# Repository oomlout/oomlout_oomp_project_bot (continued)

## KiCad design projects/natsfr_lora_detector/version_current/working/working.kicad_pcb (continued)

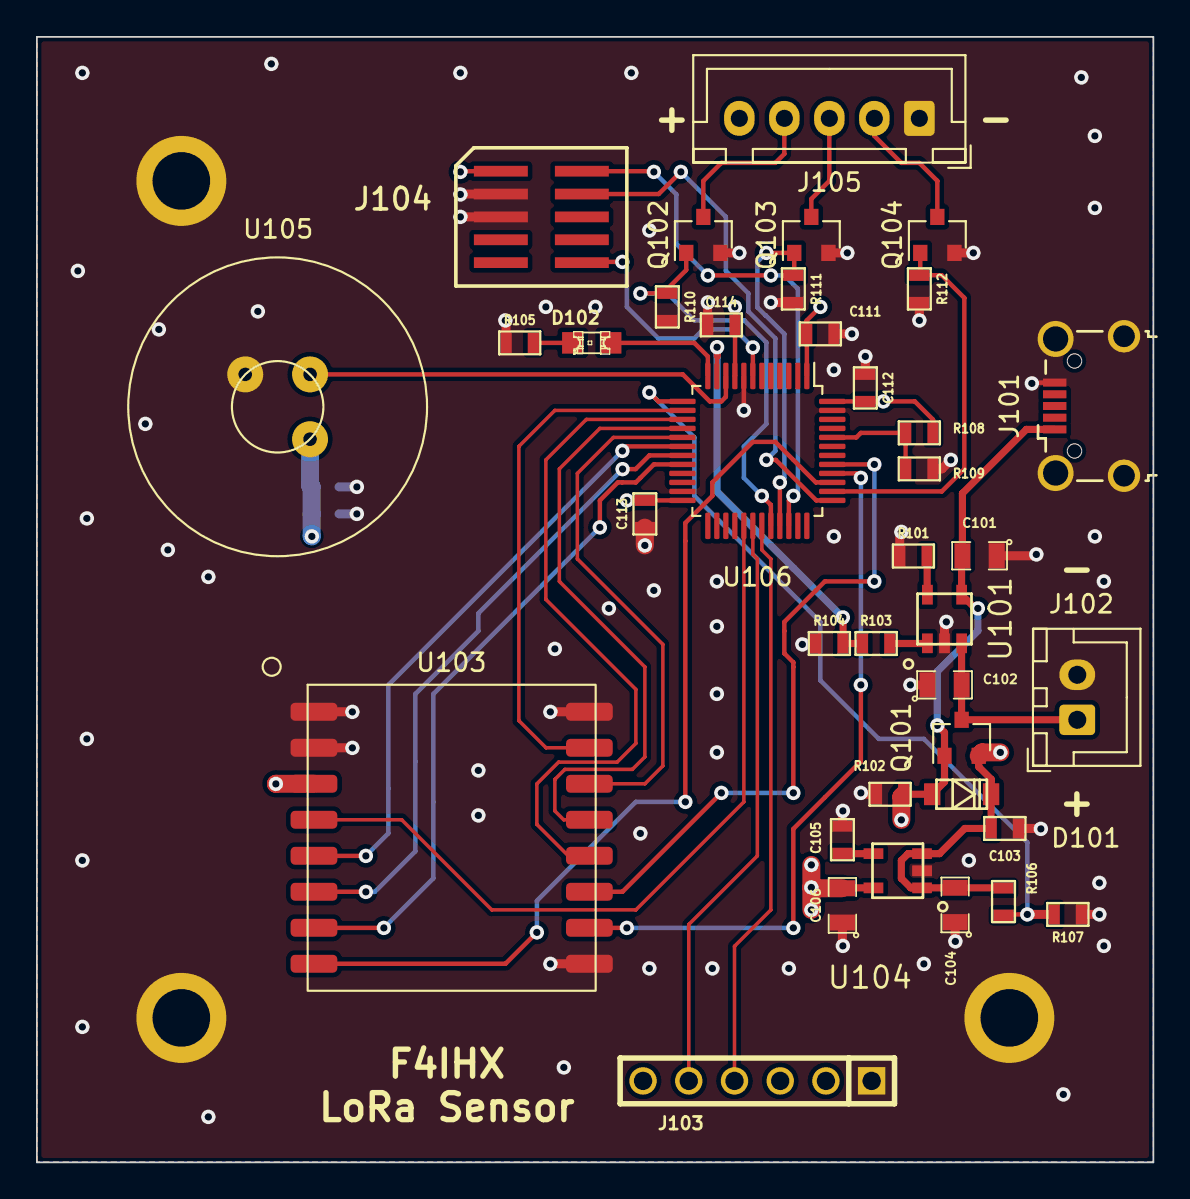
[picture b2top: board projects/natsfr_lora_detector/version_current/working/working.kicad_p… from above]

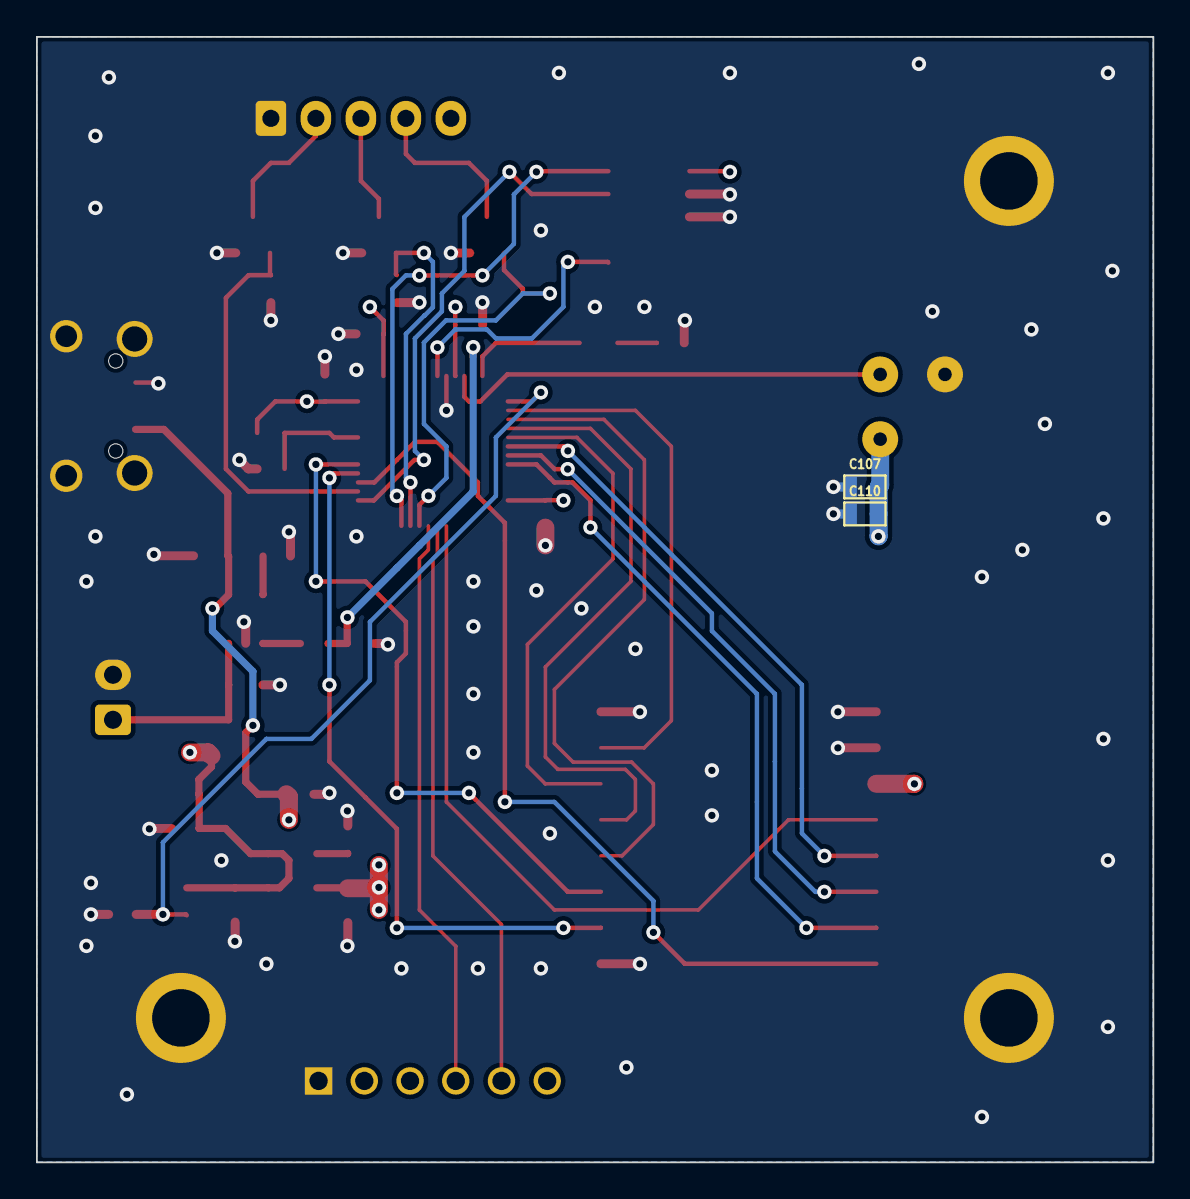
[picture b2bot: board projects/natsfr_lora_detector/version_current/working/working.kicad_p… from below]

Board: 4 copper layers, 62.0 x 62.5 mm, 40 parts (2 on the bottom side), 36 nets.

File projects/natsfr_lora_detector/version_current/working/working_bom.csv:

"Id";"Designator";"Footprint";"Quantity";"Designation";"Supplier and ref";
1;"C111,C113,C114,C112,C110,C107";"SM0603";6;"100nF";;;
2;"R110,R112,R111,R104";"SM0603";4;"10k";;;
3;"C103";"SM0603";1;"1uF";;;
4;"J102";"JST_XH_B2B-XH-A_1x02_P2.50mm_Vertical";1;"Battery";;;
5;"C101,C104,C106,C102";"SM0805";4;"4.7uF";;;
6;"D101";"SOD-123";1;"SCHOTTKY";;;
7;"J101";"USB_Micro-B_Wuerth_629105150521_CircularHoles";1;"USB_OTG";;;
8;"Q103,Q104,Q102";"SOT-23";3;"BSS138";;;
9;"REF**,REF**,REF**";"3.2mm_plated";3;"3.2mm_plated";;;
10;"R106,R101,R102,R109,R107";"SM0603";5;"12k";;;
11;"R108";"SM0603";1;"NC";;;
12;"C105";"SM0603";1;"10nF";;;
13;"U105";"EKMB439311xK";1;"EKMB439311xK";;;
14;"J105";"JST_XH_B5B-XH-A_1x05_P2.50mm_Vertical";1;"Conn_01x05";;;
15;"R105";"SM0603";1;"220";;;
16;"J103";"pin_array_6x1";1;"Conn_01x06_Male";;;
17;"J104";"JTAG_10ARM";1;"ARM_10x2mm";;;
18;"R103";"SM0603";1;"6.8k";;;
19;"D102";"LED-0805";1;"LED";;;
20;"U104";"SOT23-5";1;"REG113-XX-SOT23";;;
21;"U101";"SOT23-5";1;"MCP73821_2_SOT-23-5";;;
22;"U103";"RA-02_Lora";1;"RA-02_uFL";;;
23;"U106";"LQFP-48_7x7mm_P0.5mm";1;"STM32F051C8Tx";;;
24;"Q101";"SOT-23";1;"IRLML2244";;;

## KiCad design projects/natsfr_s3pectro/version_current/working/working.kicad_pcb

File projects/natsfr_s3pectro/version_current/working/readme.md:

# OOMP Project  
## s3pectro  by natsfr  
  
oomp key: oomp_projects_flat_natsfr_s3pectro  
(snippet of original readme)  
  
- s3pector  
Solid State Spectrometer front end  
  
  full source readme at [readme_src.md](readme_src.md)  
  
source repo at: [https://github.com/natsfr/s3pectro](https://github.com/natsfr/s3pectro)  
## Board  

## Schematic  

[schematic pdf](working_schematic.pdf)  
## Images

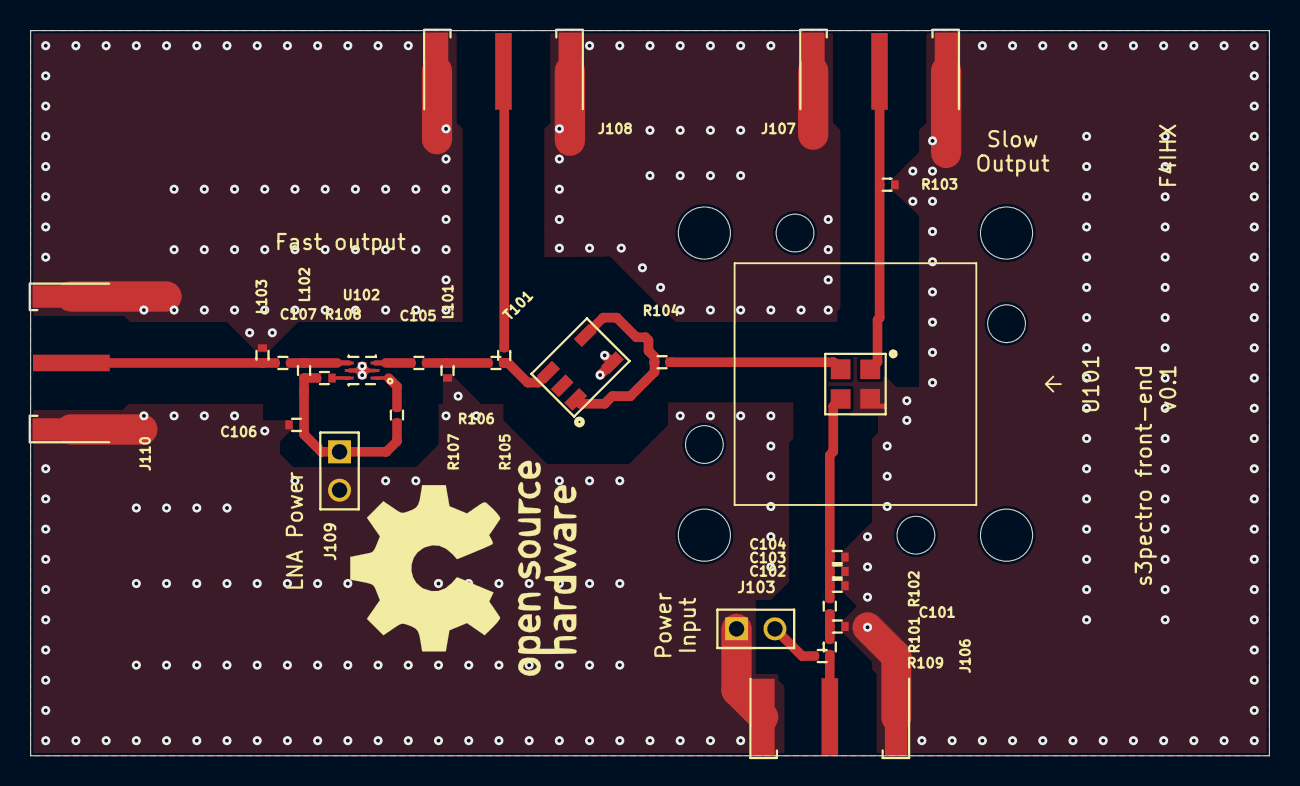
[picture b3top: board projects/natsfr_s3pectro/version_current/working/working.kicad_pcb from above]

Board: 4 copper layers, 82.0 x 48.0 mm, 32 parts (0 on the bottom side), 17 nets.

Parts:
C101, C102, C103, C104: 10n; SM0402
C105, C107: 33p; SM0402
C106: 100nF; SM0402
J101, J102, J104, J105: Conn_01x01; 3.45MM_NOTPLATED
J103, J109: Conn_01x02; pin_array_2x1
J106, J107, J108, J110: SMA_142-0701-801; CINCH_142-0701-801
L101: 18nH; SM0402
L102: 33nH; SM0402
L103: NC; SM0402
R101, R102, R103: 49.9R; SM0402
R104, R105, R106, R109: 0R; SM0402
R107, R108: 75R; SM0402
T101: MABACT0059
U101: MICROFB-30035; MicroFC-30035-SMT
U102: GRF2133; DFN-6_EP_1.5x1.5_Pitch0.5mm

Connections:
/LEN: R107.2, U102.1
/LNA_POW: C106.1, J109.1, L102.2, R107.1, R108.2
/LNA_Vdd: R108.1, U102.6
/RF_slow_out: J107.1, R103.1, U101.1
/RFo: R104.1, U101.2
/RFo_0: C107.2, J110.1, L103.2
/RFo_1: C107.1, L102.1, U102.4
/RFo_2: C105.2, U102.3
/RFo_3: C105.1, L101.2, R106.2
/RFo_4: R105.1, R106.1, T101.3
/RFo_n: J108.1, R105.2
/RFo_t: R104.2, T101.1, T101.4
/RFpi: C102.2, C103.2, C104.2, R102.2, U101.3
/RFpi_0: J106.1, R101.1, R109.2
/RFpi_1: C101.2, R101.2, R102.1
/RFpi_p: J103.2, R109.1
GND: C101.1, C102.1, C103.1, C104.1, C106.2, J103.1, J106.2, J107.2, J108.2, J109.2, J110.2, L101.1, L103.1, R103.2, T101.5, U101.4, U102.2, U102.5, U102.7

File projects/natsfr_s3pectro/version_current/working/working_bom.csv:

"Id";"Designator";"Footprint";"Quantity";"Designation";"Supplier and ref";
1;"J102,J105,J104,J101";"3.45MM_NOTPLATED";4;"Conn_01x01";;;
2;"R109,R106,R105,R104";"SM0402";4;"0R";;;
3;"R108,R107";"SM0402";2;"75R";;;
4;"R103,R102,R101";"SM0402";3;"49.9R";;;
5;"L103";"SM0402";1;"NC";;;
6;"L102";"SM0402";1;"33nH";;;
7;"L101";"SM0402";1;"18nH";;;
8;"C107,C105";"SM0402";2;"33p";;;
9;"C106";"SM0402";1;"100nF";;;
10;"C104,C103,C102,C101";"SM0402";4;"10n";;;
11;"G***";"OpenHardware";1;"LOGO";;;
12;"REF**,REF**,REF**,REF**";"2.5mm_non_plated";4;"2.5mm_non_plated";;;
13;"J109,J103";"pin_array_2x1";2;"Conn_01x02";;;
14;"U101";"MicroFC-30035-SMT";1;"MICROFB-30035";;;
15;"U102";"DFN-6_EP_1.5x1.5_Pitch0.5mm";1;"GRF2133";;;
16;"T101";"MABACT0059";1;"MABACT0059";;;
17;"J110,J108,J107,J106";"CINCH_142-0701-801";4;"SMA_142-0701-801";;;

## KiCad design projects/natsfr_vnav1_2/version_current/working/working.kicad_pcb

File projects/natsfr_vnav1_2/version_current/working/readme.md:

# VNAV1.2 by natsfr  
This is a harvested standardized copy of a project from github.  
The original project can be found at:  
https://github.com/natsfr/VNAV1.2  
Please consult that link for additional, details, files, and license information.  
Note: It was auto harvested and if the original repo had more than one board file or anything out of the ordinary the files here are likely not representative.

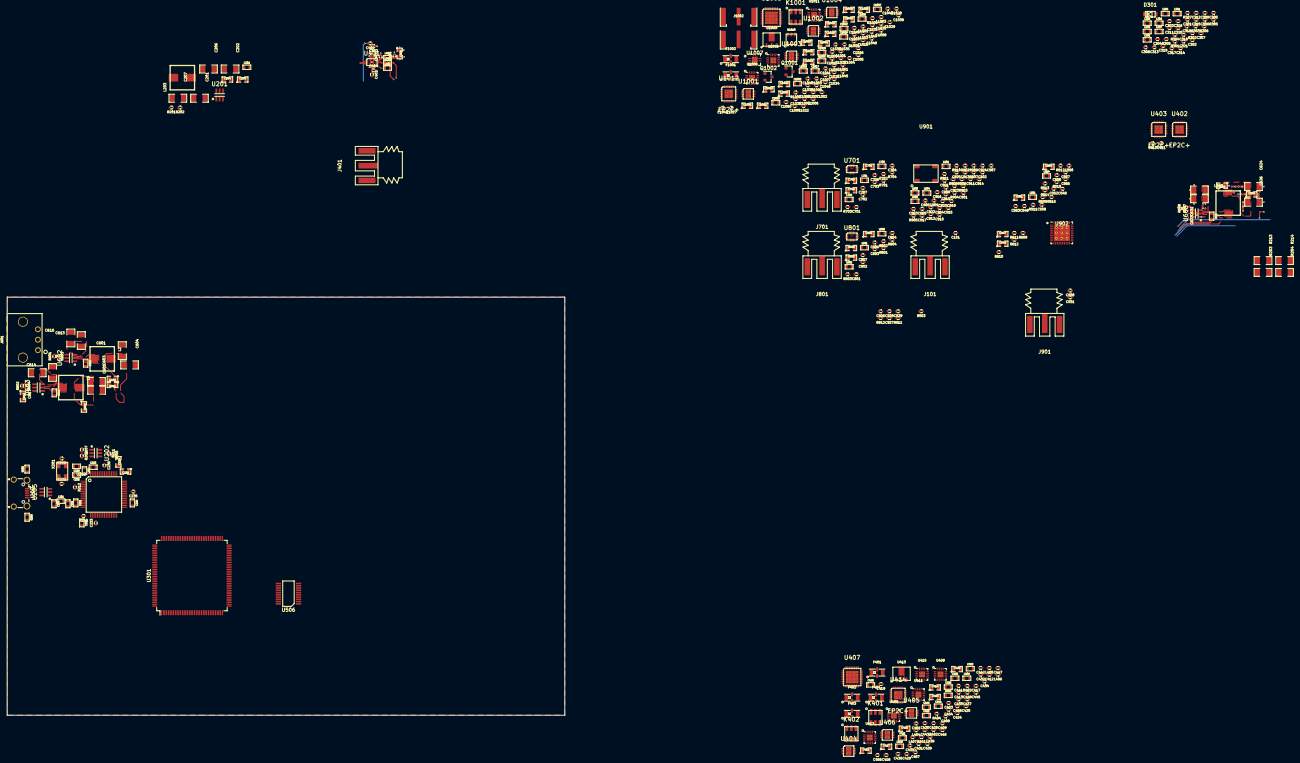
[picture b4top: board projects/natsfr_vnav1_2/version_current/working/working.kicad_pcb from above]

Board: 4 copper layers, 160.0 x 120.0 mm, 419 parts (1 on the bottom side), 264 nets.

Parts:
C101, C401, C402, C403, C404, C406, C407, C410, C411, C701, C702, C703, C704, C706, C707, C801, C802, C803, C804, C806, C807: CAP_0402; SM0402
C201, C202, C206, C207, C601, C603, C604, C605, C613, C614, C616, C617, C624, C626, C631, C633: 10uF; SM1206
C204, C608, C609, C628: 100nF; SM0805
C205, C611, C612, C630, C1050, C1051, C1053, C1056: 1uF; SM0805
C208, C618, C619, C637: 100nF; SM0603
C221, C223, C224: 100n; SM0603
C222, C226: 10p; SM0402
C225, C229: 4.7u; SM0805
C227: 1uF; SM0603
C228, C230, C231, C232: CAP_0603; SM0603
C233, C234, C235, C236: 100n; SM0402
C301, C302, C304, C305, C307, C308, C310, C311, C313, C314, C316, C317, C319, C320, C548, C549, C550, C552, C555, C901, C902, C904, C906, C907, C908, C909, C911, C912, C914, C916, C919, C920, C923, C926, C927, C928, C929: 10nF; SM0402
C303, C306, C309, C312, C315, C318, C321, C433, C434, C441, C553, C556, C903, C905, C910, C913, C915, C917, C922, C924: 100pF; SM0402
C405, C705, C805: CAP_0805; SM0805
C408, C412, C424, C429, C430, C432, C438, C440, C557, C921, C925, C930, C931, C1001, C1003, C1015, C1021, C1022, C1028, C1032, C1034, C1041: 100nF; SM0402
C409, C413, C417, C425, C431, C437, C439, C443, C558, C1002, C1004, C1005, C1016, C1027, C1031, C1033, C1036, C1037, C1040, C1055, C1059, C1060, C1061: 10pF; SM0402
C414, C415, C416, C426, C427, C428, C1008, C1009, C1010, C1011, C1023, C1024, C1025, C1026: 10uF; SM0805
C418, C1006: 390pF; SM0402
C419, C1007: 33nF; SM0402
C420, C1012: 1500pF; SM0402
C421, C422, C423, C1017, C1018, C1019, C1020: 1nF; SM0603
C435, C436, C442, C454, C456, C457, C458, C1029, C1030, C1035, C1049, C1054: 22pF; SM0402
C444, C446, C448, C450, C452, C455, C1038, C1047, C1052, C1057: 47nF; SM0603
C445, C447, C449, C451, C453, C1039, C1048, C1058: 22p; SM0402
C551, C554: 4.7uF; SM0805
C646, C647, C708, C709, C808, C809: 100uF; SM0805
C918: 15pF; SM0402
C1042, C1043, C1046: 1nF; SM0402
C1044: 5.6pF; SM0402
C1045: 18pF; SM0402
D301: DIODE; SOD-123
F401: LFCN-2500+; FV1206
F402, F1001: LFCN-7200+; FV1206
F403: LFCN-1400+; FV1206
F404, F1002: LFCN-5000+; FV1206
J101, J901: LO Ref output; SMA_AMP_132255-12
J202: USB_OTG; USB_Micro-B_Wuerth_629105150521_CircularHoles
J401, J701, J801: SMA_PCB; SMA_AMP_132255-12
J601: Conn_01x03; MICROFIT_3POS_FEM_43650-0303
J1001: DUT_OUT_1; CINCH_142-0701-881
J1002: DUT_OUT_2; CINCH_142-0701-881
K401, K402, K1001: TCM1-83X-1+; DB1627
L2, L3, L203, L603: 2.2uH; IND_7x7x4.5
L201, L202, L401, L402, L403, L701, L702, L703, L801, L802, L803: IND_0603; SM0603
L301, L302, L303, L304, L305, L306, L307, L501, L514, L901, L902, L903, L904: BLM18; SM0603
L404, L405, L406, L407, L1001, L1002: 7.5nH; SM0402
L408, L1006: 33n; SM0603
L1003: NC; SM0402
L1004, L1005: IND_0805; SM0805
Q1001: BSS84; SOT-23
Q1002: BSS138; SOT-23
R201, R207, R208, R211, R306, R307, R601, R602, R607, R1007, R1008, R1009: 10k; SM0402
R202: 65k; SM0402
R203, R204, R213, R214: RES_1206; SM1206
R205, R206: NP; SM0603
R209: 2.2k; SM0402
R210, R403, R509, R510, R511, R512, R513, R514, R903, R904, R905, R906, R1004: 1k; SM0402
R212: 12k; SM0402
R301, R302, R303, R304, R305, R308, R515, R612, R704, R804: 0; SM0402
R401, R404, R1001, R1002, R1005: 4.7k; SM0402
R402, R901, R902, R1003: RES_0402; SM0402
R405: 49; SM0603
R503, R907, R908, R909, R910: 50; SM0402
R603: 31.6k; SM0402
R604: 4.99k; SM0402
R608: 52.3k; SM0402
R609, R610, R701, R702, R801, R802: 25; SM0402
R611, R703, R803: DNI; SM0402
R911, R912: 100; SM0402
R1006: 38; SM0603
U201, U602, U603, U606: TPS563208_SOT236; SOT-236-095mm
U202: 93LC46B; SOT-236-095mm
U203: FT2232H; LQFP_64
U205: TPD4E1U06-SC70; SOT-236-095mm
U301: ICE40HX1K-TQ144; TQFP-144_20x20mm_P0.5mm
U401, U701, U801: LTC5548; QFN12_2x3mm_UDB_LT
U402, U403, U414, U1012: EP2C+; QFN24_4x4_0.5mm
U404, U1001, U1002: ADM7170ACPZ-5.0; DFN8_3x3mm
U405, U406, U1003, U1004: ADM7170ACPZ-3.3; DFN8_3x3mm
U407: ADF4355; QFN32_5x5mm_3.6mm
U408, U409, U410, U411, U412, U1006, U1008: PE42553; QFN-16_EP_3x3_Pitch0.5mm
U413, U1009: SKY65013-70LF; SOT89-SKY65013-70
U506: ADS131M03_TSSOP; TSSOP20_5.8W
U901: 16.384MHz; IQD_CFPT-126
U902: SI5332A-D-GM2; SI5332A_QFN40_EP_5.9x5.9_Pitch0.5mm
U1005: ADF5355; QFN32_5x5mm_3.6mm
U1007: TSS-183A+; DQ849
U1010: LTC1983; SOT23-6
U1011: PE42520; QFN-16_EP_3x3_Pitch0.5mm
X201: TXC_50X32_AB; XTAL_5.0x3.2mm

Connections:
+1V2: C304.1, C307.1, C603.1, L302.2, L303.2, R203.1, R604.1
+3.3VA: C228.1, C229.2, C230.1, C233.1, C234.1, C235.1, C236.1, C301.1, C310.1, C313.1, C316.1, C319.1, C405.2, C406.2, C551.1, C554.2, C601.1, C705.2, C706.2, C805.2, C806.2, C901.1, C906.1, C907.1, C911.1, C919.1, C1056.2, D301.A, L201.1, L202.1, L301.2, L304.2, L305.2, L306.2, L307.2, L401.2, L501.2, L514.2, L701.2, L801.2, L901.2, L902.2, L903.2, L904.2, Q1001.2 (S), R204.1, R207.2, R208.2, R210.2, R211.2, R306.1, R307.1, R603.1, R611.1, R703.1, R803.1, R905.1, R906.1, U202.6 (VCC), U203.20 (VCCIO), U203.31 (VCCIO), U203.42 (VCCIO), U203.50 (VREGIN), U203.56 (VCCIO), U902.4 (VDD_XTAL)
+5V: C624.1, R213.1, R608.1
+6V: C201.1, C414.1, C415.1, C416.1, C1008.1, C1009.1, C1010.1, C1011.1, R214.1, U404.7 (Vin), U404.8 (Vin), U405.7 (Vin), U405.8 (Vin), U406.7 (Vin), U406.8 (Vin), U1001.7 (Vin), U1001.8 (Vin), U1002.7 (Vin), U1002.8 (Vin), U1003.7 (Vin), U1003.8 (Vin), U1004.7 (Vin), U1004.8 (Vin)
+12V: C206.1, C207.1, C613.1, C614.1, C616.1, C617.1, C631.1, C633.1, J601.1, U201.3 (VIN), U201.5 (EN), U602.3 (VIN), U602.5 (EN), U603.3 (VIN), U603.5 (EN), U606.3 (VIN), U606.5 (EN)
/ADC/A0_N: C809.2, R510.1, R802.1
/ADC/A0_P: C808.2, R509.1, R801.2
/ADC/A1_N: C709.2, R511.1, R702.1
/ADC/A1_P: C708.2, R512.1, R701.2
/ADC/A2_N: C647.2, R514.1, R610.1
/ADC/A2_P: C646.2, R513.1, R609.2
/ADC/DIN: U301.48 (IOB_33), U506.16 (DIN)
/ADC/DOUT: U301.47 (IOB_32), U506.15 (DOUT)
/ADC/SCLK: U301.49 (IOB_35_GBIN5), U506.14 (SCLK)
/ADC/~CS: U301.45 (IOB_31), U506.12 (~CS)
/ADC/~DRDY: U301.44 (IOB_30), U506.13 (~DRDY)
/ADC/~SYNC/RST: U301.43 (IOB_29), U506.11 (~SYNC/RESET)
/ADC_CLK: R515.2, R910.2
/ANALOG_EN: R401.2, R1001.2, R1002.2, U301.22 (IOL_7B), U404.5 (EN), U405.5 (EN), U406.5 (EN), U1001.5 (EN), U1002.5 (EN), U1003.5 (EN), U1004.5 (EN)
/Clocking/FILT_3V3: C902.1, C903.2, C904.1, C905.2, C908.1, C910.2, C912.1, C913.2, C916.1, C917.2, C920.1, C922.2, L901.1, U902.15 (VDDO0), U902.18 (VDDO1), U902.25 (VDDO2), U902.28 (VDDO3), U902.33 (VDDO4), U902.40 (VDDO5)
/Clocking/SCLK: R905.2, U301.34 (IOL_12B), U902.11 (SCLK)
/Clocking/SDATA: R906.2, U301.33 (IOL_12A), U902.12 (SDATA)
/FPGA/D_N: J202.2 (D-), U203.7 (DM), U205.4 (D2-)
/FPGA/D_P: J202.3 (D+), U203.8 (DP), U205.6 (D1-)
/FPGA/F_CLKOUT: U203.32 (ACBUS5), U301.128 (IOT_84_GBIN1)
/FPGA/F_OE: U203.33 (ACBUS6), U301.120 (IOT_81)
/FPGA/F_RD: U203.28 (ACBUS2), U301.129 (IOT_85_GBIN0)
/FPGA/F_RXF: U203.26 (ACBUS0), U301.135 (IOT_88)
/FPGA/F_SIWU: U203.30 (ACBUS4), U301.121 (IOT_82)
/FPGA/F_TXE: U203.27 (ACBUS1), U301.134 (IOT_87)
/FPGA/F_WR: U203.29 (ACBUS3), U301.122 (IOT_83)
/FPGA/ICE40_DONE: R308.1, U203.45 (BDBUS6)
/FPGA/LO_CLK: U301.29 (IOL_10B), U407.1 (CLK)
/FPGA/LO_DATA: U301.28 (IOL_10A), U407.2 (DATA)
/FPGA/LO_LE: U301.31 (IOL_11A), U407.3 (LE)
/FPGA/LO_LOCK: U301.32 (IOL_11B), U407.30 (MUXOUT)
/FPGA/SIGGEN_CLK: U301.24 (IOL_8B), U1005.1 (CLK)
/FPGA/SIGGEN_DATA: U301.23 (IOL_8A), U1005.2 (DATA)
/FPGA/SIGGEN_LE: U301.25 (IOL_9A), U1005.3 (LE)
/FPGA/SIGGEN_LOCK: U301.26 (IOL_9B), U1005.30 (MUXout)
/FPGA/SPI_CLK: R303.2, U203.38 (BDBUS0)
/FPGA/SPI_MISO: R301.2, U203.40 (BDBUS2)
/FPGA/SPI_MOSI: R302.2, U203.39 (BDBUS1)
/FPGA/fd0: U203.16 (ADBUS0), U301.144 (IOT_96)
/FPGA/fd1: U203.17 (ADBUS1), U301.143 (IOT_95)
/FPGA/fd2: U203.18 (ADBUS2), U301.142 (IOT_94)
/FPGA/fd3: U203.19 (ADBUS3), U301.141 (IOT_93)
/FPGA/fd4: U203.21 (ADBUS4), U301.139 (IOT_92)
/FPGA/fd5: U203.22 (ADBUS5), U301.138 (IOT_91)
/FPGA/fd6: U203.23 (ADBUS6), U301.137 (IOT_90)
/FPGA/fd7: U203.24 (ADBUS7), U301.136 (IOT_89)
/FPGA/~ICE40_RST: R305.2, U203.46 (BDBUS7)
/FPGA/~SPI_CS: R304.2, U203.43 (BDBUS4)
/FPGA_CLK: R908.2, U301.50 (IOB_36_GBIN4)
/LO_BANDSEL: U301.11 (IOL_5A), U412.14 (CTRL)
/LO_HB1: U301.8 (IOL_3B), U409.14 (CTRL)
/LO_HB2: U301.10 (IOL_4B), U411.14 (CTRL)
/LO_LB1: U301.7 (IOL_3A), U408.14 (CTRL)
/LO_LB2: U301.9 (IOL_4A), U410.14 (CTRL)
/Mixer DUT1/dut_lo: C701.2, C702.1, U701.11 (LO)
/Mixer DUT1/dut_rf: C703.2, C704.2, U701.5 (RF)
/Mixer DUT1/dut_rf_0: C703.1, J701.1 (sig)
/Mixer DUT1/mx_d_3v3: C707.2, L701.1, U701.9 (Vcc)
/Mixer DUT2/dut_lo: C801.2, C802.1, U801.11 (LO)
/Mixer DUT2/dut_rf: C803.2, C804.2, U801.5 (RF)
/Mixer DUT2/dut_rf_0: C803.1, J801.1 (sig)
/Mixer DUT2/mx_d_3v3: C807.2, L801.1, U801.9 (Vcc)
/Mixer DUT/dut_lo: C401.2, C402.1, U401.11 (LO)
/Mixer DUT/dut_rf: C403.2, C404.2, U401.5 (RF)
/Mixer DUT/dut_rf_0: C403.1, J401.1 (sig)
/Mixer DUT/mx_d_3v3: C407.2, L401.1, U401.9 (Vcc)
/OUTPUT_PA_ON: Q1001.1 (G), R1007.1, U301.21 (IOL_7A_GBIN6)
/PLL DUT/-5V: C1051.1, Q1002.2 (S), R1008.2, U1010.2 (Vout)
/PLL DUT/D1_0: C1060.2, J1001.1 (sig)
/PLL DUT/D1_1: C1060.1, U1012.19 (RF1)
/PLL DUT/D2_0: C1061.2, J1002.1 (sig)
/PLL DUT/D2_1: C1061.1, U1012.12 (RF2)
/PLL DUT/D_0: C1059.2, U1012.3 (RFS)
/PLL DUT/D_1: C1059.1, U1011.7 (RFC)
/PLL DUT/D_HB_0: C1055.2, U1011.11 (RF2)
/PLL DUT/D_HB_1: C1055.1, U1007.5 (RFOUT)
/PLL DUT/D_HB_2: C1040.2, U1007.2 (RFIN)
/PLL DUT/D_HB_3: C1037.2, C1040.1, L1003.1
/PLL DUT/D_HB_4: C1037.1, U1005.14 (RFoutB)
/PLL DUT/D_LB_0: C1054.2, U1011.2 (RF1)
/PLL DUT/D_LB_1: C1054.1, L1006.2, U1009.3 (OUT)
/PLL DUT/D_LB_2: C1049.2, U1009.1 (IN)
/PLL DUT/D_LB_3: C1049.1, U1008.7 (RFC)
/PLL DUT/D_LB_4: C1035.2, U1006.7 (RFC)
/PLL DUT/D_LB_5: C1035.1, K1001.3 (PDOT)
/PLL DUT/D_LB_H_0: F1001.3 (RFOUT), U1008.11 (RF2)
/PLL DUT/D_LB_H_1: F1001.1 (RFIN), U1006.2 (RF1)
/PLL DUT/D_LB_L_0: F1002.3 (RFOUT), U1008.2 (RF1)
/PLL DUT/D_LB_L_1: F1002.1 (RFIN), U1006.11 (RF2)
/PLL DUT/VG_AMP: C1043.1, L1005.2, Q1002.3 (D), R1009.2, U1007.4 (VG2)
/PLL DUT/Vamp: C1050.1, U1010.1 (Vcc), U1010.6 (~SHDN)
/PLL DUT/Vtune: C1006.1, R1003.1, U1005.20 (VTune)
/PLL DUT/Vvco: C1005.1, C1024.1, C1028.1, C1031.1, U1002.1 (Vout), U1002.2 (Vout), U1002.3 (Sense), U1005.6 (Vp), U1005.17 (Vvco), U1005.19 (Vregvco)
/PLL DUT/p_a_0_N: C1029.1, L1002.2, U1005.12 (RFoutA-)
/PLL DUT/p_a_0_P: C1030.2, L1001.2, U1005.11 (RFoutA+)
/PLL DUT/p_a_1_N: C1029.2, K1001.5 (SDOT)
/PLL DUT/p_a_1_P: C1030.1, K1001.4 (S)
/PLL DUT/pll_3v3: C1001.1, C1002.1, C1003.1, C1004.1, C1022.1, C1025.1, C1027.1, U1003.1 (Vout), U1003.2 (Vout), U1003.3 (Sense), U1005.4 (CE), U1005.5 (Avdd), U1005.16 (Avdd), U1005.26 (PDBrf), U1005.27 (Dvdd)
/PLL DUT/pll_vrf: C1016.1, C1026.1, L1001.1, L1002.1, U1004.1 (Vout), U1004.2 (Vout), U1004.3 (Sense), U1005.10 (Vrf)
/PLL/LO_0: C401.1, C456.2, U403.19 (RF1), U414.3 (RFS)
/PLL/LO_1: C456.1, C701.1, L408.2, U403.12 (RF2), U413.3 (OUT)
/PLL/LO_1_1: C458.1, U414.12 (RF2)
/PLL/LO_2: C101.1, C454.2, U402.19 (RF1), U413.1 (IN)
/PLL/LO_2_1: C457.1, U414.19 (RF1)
/PLL/LO_3: C454.1, C801.1, U402.12 (RF2), U412.7 (RFC)
/PLL/LO_HH_0: F402.3 (RFOUT), U411.11 (RF2)
/PLL/LO_HH_1: F402.1 (RFIN), U409.2 (RF1)
/PLL/LO_HL_0: F404.3 (RFOUT), U411.2 (RF1)
/PLL/LO_HL_1: F404.1 (RFIN), U409.11 (RF2)
/PLL/LO_H_0: U411.7 (RFC), U412.11 (RF2)
/PLL/LO_H_1: C442.2, U409.7 (RFC)
/PLL/LO_H_2: C442.1, K402.3 (PDOT)
/PLL/LO_LH_0: F401.3 (RFOUT), U410.11 (RF2)
/PLL/LO_LH_1: F401.1 (RFIN), U408.2 (RF1)
/PLL/LO_LL_0: F403.3 (RFOUT), U410.2 (RF1)
/PLL/LO_LL_1: F403.1 (RFIN), U408.11 (RF2)
/PLL/LO_L_0: U410.7 (RFC), U412.2 (RF1)
/PLL/LO_L_1: C441.2, U408.7 (RFC)
/PLL/LO_L_2: C441.1, K401.3 (PDOT)
/PLL/Vtune: C418.1, R402.1, U407.20 (Vtune)
/PLL/Vvco: C417.1, C426.1, C432.1, C437.1, U404.1 (Vout), U404.2 (Vout), U404.3 (Sense), U407.6 (Vp), U407.17 (Vvco), U407.19 (Vregvco)
/PLL/XO_N: C927.2, U407.28 (REFinB)
/PLL/XO_P: C926.2, U407.29 (REFinA)
/PLL/p_a_0_N: C435.1, L407.2, U407.15 (RfoutB-)
/PLL/p_a_0_P: C436.2, L405.2, U407.14 (RfoutB+)
/PLL/p_a_1_N: C435.2, K402.5 (SDOT)
/PLL/p_a_1_P: C436.1, K402.4 (S)
/PLL/p_b_0_N: C433.1, L406.2, U407.12 (RfoutA-)
/PLL/p_b_0_P: C434.2, L404.2, U407.11 (RfoutA+)
/PLL/p_b_1_N: C433.2, K401.5 (SDOT)
/PLL/p_b_1_P: C434.1, K401.4 (S)
/PLL/pll_3v3: C408.1, C409.1, C412.1, C413.1, C427.1, C430.1, C431.1, U405.1 (Vout), U405.2 (Vout), U405.3 (Sense), U407.4 (CE), U407.5 (Avdd), U407.16 (Avdd), U407.26 (PDBrf), U407.27 (Dvdd)
/PLL/pll_vrf: C425.1, C428.1, L404.1, L405.1, L406.1, L407.1, U406.1 (Vout), U406.2 (Vout), U406.3 (Sense), U407.10 (Vrf)
/PSU/1V2_SW: C619.1, L3.2, U603.2 (SW)
/PSU/3V3_SW: C618.1, L2.2, U602.2 (SW)
/PSU/5V_SW: C637.1, L603.2, U606.2 (SW)
/PSU/6V_SW: C208.1, L203.2, U201.2 (SW)
/SIGGEN_BANDSEL: U301.20 (IOL_6B_GBIN7), U1011.14 (CTRL)
/SIGGEN_CLK_N: C929.2, U1005.28 (REFinB)
/SIGGEN_CLK_P: C928.2, U1005.29 (REFinA)
/SIGGEN_LB1: U301.19 (IOL_6A), U1006.14 (CTRL)
/SIGGEN_LB2: U301.12 (IOL_5B), U1008.14 (CTRL)
GND: C201.2, C202.2, C204.2, C205.2, C206.2, C207.2, C221.2, C222.2, C223.2, C224.2, C225.1, C226.2, C227.2, C228.2, C229.1, C230.2, C231.2, C232.2, C233.2, C234.2, C235.2, C236.2, C301.2, C302.2, C303.1, C304.2, C305.2, C306.1, C307.2, C308.2, C309.1, C310.2, C311.2, C312.1, C313.2, C314.2, C315.1, C316.2, C317.2, C318.1, C319.2, C320.2, C321.1, C402.2, C404.1, C405.1, C406.1, C407.1, C408.2, C409.2, C412.2, C413.2, C414.2, C415.2, C416.2, C417.2, C418.2, C420.2, C421.2, C422.2, C423.2, C424.2, C425.2, C426.2, C427.2, C428.2, C429.1, C430.2, C431.2, C432.2, C437.2, C438.2, C439.2, C440.2, C443.2, C444.1, C445.1, C446.1, C447.1, C448.1, C449.1, C450.1, C451.1, C452.1, C453.1, C455.1, C551.2, C552.2, C553.1, C554.1, C555.2, C556.1, C557.1, C558.1, C601.2, C603.2, C604.2, C605.2, C608.2, C609.2, C611.2, C612.2, C613.2, C614.2, C616.2, C617.2, C624.2, C626.2, C628.2, C630.2, C631.2, C633.2, C702.2, C704.1, C705.1, C706.1, C707.1, C802.2, C804.1, C805.1, C806.1, C807.1, C901.2, C902.2, C903.1, C904.2, C905.1, C906.2, C907.2, C908.2, C909.2, C910.1, C911.2, C912.2, C913.1, C914.2, C915.1, C916.2, C917.1, C918.2, C919.2, C920.2, C922.1, C923.2, C924.1, C931.1, C1001.2, C1002.2, C1003.2, C1004.2, C1005.2, C1006.2, C1008.2, C1009.2, C1010.2, C1011.2, C1012.2, C1015.2, C1016.2, C1017.2, C1018.2, C1019.2, C1020.2, C1021.1, C1022.2, C1023.2, C1024.2, C1025.2, C1026.2, C1027.2, C1028.2, C1031.2, C1032.2, C1033.2, C1034.2, C1036.2, C1038.1, C1039.1, C1041.2, C1042.2, C1043.2, C1044.2, C1045.2, C1046.2, C1047.1, C1048.1, C1050.2, C1051.2, C1052.1, C1056.1, C1057.1, C1058.1, F401.2 (GND), F401.4 (GND), F402.2 (GND), F402.4 (GND), F403.2 (GND), F403.4 (GND), F404.2 (GND), F404.4 (GND), F1001.2 (GND), F1001.4 (GND), F1002.2 (GND), F1002.4 (GND), J101.2, J202.5 (GND), J401.2, J601.2, J601.3, J701.2, J801.2, J901.2, J1001.2, J1002.2, K401.2 (PGND), K402.2 (PGND), K1001.2 (PGND), L1003.2, R201.2, R205.2, R206.2, R212.2, R401.1, R403.2, R404.1, R503.1, R601.2, R602.2, R607.2, R612.1, R704.1, R804.1, R902.2, R904.2, R907.2, R909.2, R1001.1, R1002.1, R1004.2, R1005.1, R1007.2, R1009.1, U201.1 (GND), U202.2 (GND), U203.1 (GND), U203.5 (GND), U203.10 (AGND), U203.11 (GND), U203.13 (TEST), U203.15 (GND), U203.25 (GND), U203.35 (GND), U203.47 (GND), U203.51 (GND), U205.2 (GND), U301.5 (GND), U301.13 (GND), U301.14 (GND), U301.35 (GNDPLL), U301.59 (GND), U301.69 (GND), U301.86 (GND), U301.103 (GND), U301.132 (GND), U301.140 (GND), U401.1 (GND), U401.4 (GND), U401.6 (GND), U401.10 (GND), U401.12 (GND), U401.13 (PAD), U402.1 (GND), U402.2 (GND), U402.4 (GND), U402.5 (GND), U402.6 (GND), U402.7 (GND), U402.8 (GND), U402.9 (GND), U402.10 (GND), U402.11 (GND), U402.13 (GND), U402.14 (GND), U402.15 (GND), U402.16 (GND), U402.17 (GND), U402.18 (GND), U402.20 (GND), U402.21 (GND), U402.22 (GND), U402.23 (GND), U402.24 (GND), U402.25 (PAD), U403.1 (GND), U403.2 (GND), U403.4 (GND), U403.5 (GND), U403.6 (GND), U403.7 (GND), U403.8 (GND), U403.9 (GND), U403.10 (GND), U403.11 (GND), U403.13 (GND), U403.14 (GND), U403.15 (GND), U403.16 (GND), U403.17 (GND), U403.18 (GND), U403.20 (GND), U403.21 (GND), U403.22 (GND), U403.23 (GND), U403.24 (GND), U403.25 (PAD), U404.6 (GND), U404.9 (PAD), U405.6 (GND), U405.9 (PAD), U406.6 (GND), U406.9 (PAD), U407.8 (Cpgnd), U407.9 (Agnd), U407.13 (Agndrf), U407.18 (Agndvco), U407.21 (Agndvco), U407.31 (Sdgnd), U407.33 (PAD), U408.1 (GND), U408.3 (GND), U408.4 (GND), U408.5 (GND), U408.6 (GND), U408.8 (GND), U408.9 (GND), U408.10 (GND), U408.12 (GND), U408.13 (Vss_ext), U408.15 (LS), U408.17 (GND), U409.1 (GND), U409.3 (GND), U409.4 (GND), U409.5 (GND), U409.6 (GND), U409.8 (GND), U409.9 (GND), U409.10 (GND), U409.12 (GND), U409.13 (Vss_ext), U409.15 (LS), U409.17 (GND), U410.1 (GND), U410.3 (GND), U410.4 (GND), U410.5 (GND), U410.6 (GND), U410.8 (GND), U410.9 (GND), U410.10 (GND), U410.12 (GND), U410.13 (Vss_ext), U410.15 (LS), U410.17 (GND), U411.1 (GND), U411.3 (GND), U411.4 (GND), U411.5 (GND), U411.6 (GND), U411.8 (GND), U411.9 (GND), U411.10 (GND), U411.12 (GND), U411.13 (Vss_ext), U411.15 (LS), U411.17 (GND), U412.1 (GND), U412.3 (GND), U412.4 (GND), U412.5 (GND), U412.6 (GND), U412.8 (GND), U412.9 (GND), U412.10 (GND), U412.12 (GND), U412.13 (Vss_ext), U412.15 (LS), U412.17 (GND), U413.2 (GND), U413.4 (GND), U414.1 (GND), U414.2 (GND), U414.4 (GND), U414.5 (GND), U414.6 (GND), U414.7 (GND), U414.8 (GND), U414.9 (GND), U414.10 (GND), U414.11 (GND), U414.13 (GND), U414.14 (GND), U414.15 (GND), U414.16 (GND), U414.17 (GND), U414.18 (GND), U414.20 (GND), U414.21 (GND), U414.22 (GND), U414.23 (GND), U414.24 (GND), U414.25 (PAD), U506.2 (AGND), U506.19 (DGND), U602.1 (GND), U603.1 (GND), U606.1 (GND), U701.1 (GND), U701.4 (GND), U701.6 (GND), U701.10 (GND), U701.12 (GND), U701.13 (PAD), U801.1 (GND), U801.4 (GND), U801.6 (GND), U801.10 (GND), U801.12 (GND), U801.13 (PAD), U901.2 (GND), U902.41 (GND), U1001.6 (GND), U1001.9 (PAD), U1002.6 (GND), U1002.9 (PAD), U1003.6 (GND), U1003.9 (PAD), U1004.6 (GND), U1004.9 (PAD), U1005.8 (CPgnd), U1005.9 (Agnd), U1005.13 (Agndrf), U1005.15 (Agndrf), U1005.18 (Agndvco), U1005.21 (Agndvco), U1005.31 (SDgnd), U1005.33 (PAD), U1006.1 (GND), U1006.3 (GND), U1006.4 (GND), U1006.5 (GND), U1006.6 (GND), U1006.8 (GND), U1006.9 (GND), U1006.10 (GND), U1006.12 (GND), U1006.13 (Vss_ext), U1006.15 (LS), U1006.17 (GND), U1007.1 (NC), U1007.6 (NC), U1007.9 (GND), U1008.1 (GND), U1008.3 (GND), U1008.4 (GND), U1008.5 (GND), U1008.6 (GND), U1008.8 (GND), U1008.9 (GND), U1008.10 (GND), U1008.12 (GND), U1008.13 (Vss_ext), U1008.15 (LS), U1008.17 (GND), U1009.2 (GND), U1009.4 (GND), U1010.5 (GND), U1011.1 (GND), U1011.3 (GND), U1011.4 (GND), U1011.5 (GND), U1011.6 (GND), U1011.8 (GND), U1011.9 (GND), U1011.10 (GND), U1011.12 (GND), U1011.13 (Vss), U1011.15 (LS), U1011.17 (PAD), U1012.1 (GND), U1012.2 (GND), U1012.4 (GND), U1012.5 (GND), U1012.6 (GND), U1012.7 (GND), U1012.8 (GND), U1012.9 (GND), U1012.10 (GND), U1012.11 (GND), U1012.13 (GND), U1012.14 (GND), U1012.15 (GND), U1012.16 (GND), U1012.17 (GND), U1012.18 (GND), U1012.20 (GND), U1012.21 (GND), U1012.22 (GND), U1012.23 (GND), U1012.24 (GND), U1012.25 (PAD), X201.2 (GND), X201.4 (GND)
unnamed: C101.2, J101.1 (sig)
unnamed: C202.1, C204.1, C205.1, L203.1, R214.2
unnamed: C208.2, U201.6 (VBST)
unnamed: C221.1, C223.1, C224.1, C225.2, U203.12 (VCORE), U203.37 (VCORE), U203.49 (VREGOUT), U203.64 (VCORE)
unnamed: C222.1, U203.3 (OSCO), X201.1
unnamed: C226.1, U203.2 (OSCI), X201.3
unnamed: C227.1, R210.1, U203.14 (~RESET)
unnamed: C231.1, L201.2, U203.9 (VPLL)
unnamed: C232.1, L202.2, U203.4 (VPHY)
unnamed: C302.1, C303.2, L301.1, U301.72 (VCC_SPI)
unnamed: C305.1, C306.2, L302.1, U301.27 (VCC), U301.51 (VCC), U301.92 (VCC), U301.111 (VCC)
unnamed: C308.1, C309.2, L303.1, U301.36 (VCCPLL)
unnamed: C311.1, C312.2, L304.1, U301.123 (VCCIO_0), U301.133 (VCCIO_0)
unnamed: C314.1, C315.2, L305.1, U301.6 (VCCIO_3), U301.30 (VCCIO_3)
unnamed: C317.1, C318.2, L306.1, U301.89 (VCCIO_1), U301.100 (VCCIO_1)
unnamed: C320.1, C321.2, L307.1, U301.46 (VCCIO_2), U301.57 (VCCIO_2)
unnamed: C410.1, C458.2
unnamed: C410.2, U402.3 (RFS)
unnamed: C411.1, C457.2
unnamed: C411.2, U403.3 (RFS)
unnamed: C419.1, C420.1, R402.2, U407.7 (Cpout)
unnamed: C419.2, R403.1
unnamed: C421.1, U404.4 (SS)
unnamed: C422.1, U405.4 (SS)
unnamed: C423.1, U406.4 (SS)
unnamed: C424.1, U407.32 (Creg2)
unnamed: C429.2, U407.25 (Creg1)
unnamed: C438.1, C439.1, U407.23 (Vref)
unnamed: C440.1, C443.1, U407.24 (Vbias)
unnamed: C548.1, R510.2, U506.4 (A0_N)
unnamed: C548.2, R509.2, U506.3 (A0_P)
unnamed: C549.1, R512.2, U506.6 (A1_P)
unnamed: C549.2, R511.2, U506.5 (A1_N)
unnamed: C550.1, R514.2, U506.8 (A2_N)
unnamed: C550.2, R513.2, U506.7 (A2_P)
unnamed: C552.1, C553.2, L501.1, U506.1 (AVDD)
unnamed: C555.1, C556.2, L514.1, U506.20 (DVDD)
unnamed: C557.2, U506.18 (CAP)
unnamed: C558.2, R503.2, R515.1, U506.17 (CLKIN)
unnamed: C604.1, C608.1, C611.1, L2.1, R204.2
unnamed: C605.1, C609.1, C612.1, L3.1, R203.2
unnamed: C618.2, U602.6 (VBST)
unnamed: C619.2, U603.6 (VBST)
unnamed: C626.1, C628.1, C630.1, L603.1, R213.2
unnamed: C637.2, U606.6 (VBST)
unnamed: C646.1, U401.2 (IF_P)
unnamed: C647.1, U401.3 (IF_N)
unnamed: C708.1, U701.2 (IF_P)
unnamed: C709.1, U701.3 (IF_N)
unnamed: C808.1, U801.2 (IF_P)
unnamed: C809.1, U801.3 (IF_N)
unnamed: C909.1, L902.1, R901.2, U901.4 (Vcc)
unnamed: C914.1, C915.2, L903.1, U902.1 (VDD_DIG)
unnamed: C918.1, C921.1, U901.3 (OUT)
unnamed: C921.2, R903.2
unnamed: C923.1, C924.2, L904.1, U902.9 (VDDA)
unnamed: C925.1, R903.1, R904.1
unnamed: C925.2, U902.5 (XA_CLKIN1)
unnamed: C926.1, R911.1, U902.30 (OUT5)
unnamed: C927.1, R911.2, U902.29 (OUT5b)
unnamed: C928.1, R912.1, U902.22 (OUT2)
unnamed: C929.1, R912.2, U902.21 (OUT2b)
unnamed: C930.1, J901.1 (sig)
unnamed: C1007.1, C1012.1, R1003.2, U1005.7 (CPout)
unnamed: C1007.2, R1004.1
unnamed: C1015.1, U1005.32 (Creg2)
unnamed: C1017.1, U1001.4 (SS)
unnamed: C1018.1, U1002.4 (SS)
unnamed: C1019.1, U1003.4 (SS)
unnamed: C1020.1, U1004.4 (SS)
unnamed: C1021.2, U1005.25 (Creg1)
unnamed: C1032.1, C1033.1, U1005.23 (Vref)
unnamed: C1034.1, C1036.1, U1005.24 (Vbias)
unnamed: C1041.1, L1004.1, U1007.8 (VDD1)
unnamed: C1042.1, L1005.1, U1007.3 (VG1)
unnamed: C1053.1, U1010.3 (C+)
unnamed: C1053.2, U1010.4 (C-)
unnamed: D301.K, U301.108 (VPP_2V5)
unnamed: J202.6 (Shield), R205.1, R206.1
unnamed: R307.2, R308.2, U301.65 (CDONE)
unnamed: R305.1, R306.2, U301.66 (~CRESET_B)
unnamed: R304.1, U301.71 (IOB_47_SS)
unnamed: R303.1, U301.70 (IOB_46_SCK)
unnamed: R302.1, U301.68 (IOB_45_SDI)
unnamed: R301.1, U301.67 (IOB_44_SDO)
unnamed: L402.1, U401.7 (EN)
unnamed: L403.1, U401.8 (X2)
unnamed: L408.1, R405.2
unnamed: L702.1, U701.7 (EN)
unnamed: L703.1, U701.8 (X2)
unnamed: L802.1, U801.7 (EN)
unnamed: L803.1, U801.8 (X2)
unnamed: L1006.1, R1006.2
unnamed: Q1001.3 (D), Q1002.1 (G), R1008.1
unnamed: R201.1, R202.2, U201.4 (VFB)
unnamed: R207.1, R209.2, U202.1 (DOUT)
unnamed: R208.1, U202.4 (SCK), U203.62 (EECLK)
unnamed: R209.1, U202.3 (DIN), U203.61 (EEDATA)
unnamed: R211.1, U202.5 (CS), U203.63 (EECS)
unnamed: R212.1, U203.6 (REF)
unnamed: R404.2, U407.22 (Rset)
unnamed: R601.1, R603.2, U602.4 (VFB)
unnamed: R602.1, R604.2, U603.4 (VFB)
unnamed: R607.1, R608.2, U606.4 (VFB)
unnamed: R609.1, R610.2, R611.2, R612.2
unnamed: R701.1, R702.2, R703.2, R704.2
unnamed: R801.1, R802.2, R803.2, R804.2
unnamed: R901.1, R902.1, U901.1 (Vcon)
unnamed: R907.1, U902.13 (OUT0b)
unnamed: R908.1, U902.14 (OUT0)
unnamed: R909.1, U902.16 (OUT1b)
unnamed: R910.1, U902.17 (OUT1)
unnamed: R1005.2, U1005.22 (Rset)
unnamed: C930.2, U902.7 (CLKIN_3)
unnamed: C931.2, U902.8 (CLKIN_3b)
VAMP: C444.2, C445.2, C446.2, C447.2, C448.2, C449.2, C450.2, C451.2, C452.2, C453.2, C455.2, C1023.1, C1038.2, C1039.2, C1044.1, C1045.1, C1046.1, C1047.2, C1048.2, C1052.2, C1057.2, C1058.2, L1004.2, R405.1, R1006.1, U408.16 (Vdd), U409.16 (Vdd), U410.16 (Vdd), U411.16 (Vdd), U412.16 (Vdd), U1001.1 (Vout), U1001.2 (Vout), U1001.3 (Sense), U1006.16 (Vdd), U1007.7 (VDD2), U1008.16 (Vdd), U1011.16 (Vdd)

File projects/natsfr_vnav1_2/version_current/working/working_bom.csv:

"Id";"Designator";"Footprint";"Quantity";"Designation";"Supplier and ref";
1;"C221,C223,C224";"SM0603";3;"100n";;;
2;"C222,C226";"SM0402";2;"10p";;;
3;"C225,C229";"SM0805";2;"4.7u";;;
4;"C227";"SM0603";1;"1uF";;;
5;"C228,C230,C231,C232";"SM0603";4;"CAP_0603";;;
6;"C401,C402,C403,C404,C406,C407";"SM0402";6;"CAP_0402";;;
7;"C405";"SM0805";1;"CAP_0805";;;
8;"C601,C603,C604,C605,C613,C614,C616,C617,C624,C626,C631,C633";"SM1206";12;"10uF";;;
9;"C608,C609,C628";"SM0805";3;"100nF";;;
10;"C611,C612,C630";"SM0805";3;"1uF";;;
11;"C618,C619,C637";"SM0603";3;"100nF";;;
12;"J202";"USB_Micro-B_Wuerth_629105150521_CircularHoles";1;"USB_OTG";;;
13;"J401,J801,J701";"SMA_AMP_132255-12";3;"SMA_PCB";;;
14;"L201,L202,L401,L402,L403";"SM0603";5;"IND_0603";;;
15;"R205,R206";"SM0603";2;"NP";;;
16;"R207,R208,R211,R601,R602,R607";"SM0402";6;"10k";;;
17;"R209";"SM0402";1;"2.2k";;;
18;"R603";"SM0402";1;"31.6k";;;
19;"R604";"SM0402";1;"4.99k";;;
20;"R608";"SM0402";1;"52.3k";;;
21;"U202";"SOT-236-095mm";1;"93LC46B";;;
22;"U203";"LQFP_64";1;"FT2232H";;;
23;"U401,U701,U801";"QFN12_2x3mm_UDB_LT";3;"LTC5548";;;
24;"U602,U603,U606,U201";"SOT-236-095mm";4;"TPS563208_SOT236";;;
25;"X201";"XTAL_5.0x3.2mm";1;"TXC_50X32_AB";;;
26;"L603,L2,L3,L203";"IND_7x7x4.5";4;"2.2uH";;;
27;"J601";"MICROFIT_3POS_FEM_43650-0303";1;"Conn_01x03";;;
28;"U205";"SOT-236-095mm";1;"TPD4E1U06-SC70";;;
29;"R210,R904,R905,R903,R513,R403,R510,R512,R509,R514,R1004,R906,R511";"SM0402";13;"1k";;;
30;"R212";"SM0402";1;"12k";;;
31;"C233,C235,C236,C234";"SM0402";4;"100n";;;
32;"L306,L501,L901,L902,L303,L307,L904,L514,L903,L302,L305,L304,L301";"SM0603";13;"BLM18";;;
33;"R1009,R307,R1008,R201,R1007,R306";"SM0402";6;"10k";;;
34;"R611,R803,R703";"SM0402";3;"DNI";;;
35;"R305,R303,R612,R308,R704,R804,R302,R301,R304,R515";"SM0402";10;"0";;;
36;"U506";"TSSOP20_5.8W";1;"ADS131M03_TSSOP";;;
37;"C1016,C417,C1033,C1055,C1059,C1005,C1036,C1002,C439,C413,C437,C1031,C1060,C1027,C1061,C1037,C1004,C431,C409,C425,C558,C443,C1040";"SM0402";23;"10pF";;;
38;"R203,R204,R214,R213";"SM1206";4;"RES_1206";;;
39;"C1017,C421,C423,C1018,C1020,C422,C1019";"SM0603";7;"1nF";;;
40;"C318,C910,C917,C553,C306,C913,C903,C315,C312,C905,C441,C556,C321,C924,C309,C915,C434,C303,C433,C922";"SM0402";20;"100pF";;;
41;"C557,C1001,C440,C1032,C412,C930,C1015,C1041,C1034,C931,C1022,C1003,C1021,C1028,C921,C438,C430,C925,C408,C424,C432,C429";"SM0402";22;"100nF";;;
42;"F402,F1001";"FV1206";2;"LFCN-7200+";;;
43;"L801,L703,L702,L802,L701,L803";"SM0603";6;"IND_0603";;;
44;"R910,R503,R909,R907,R908";"SM0402";5;"50";;;
45;"C444,C452,C1038,C1057,C455,C448,C446,C1052,C450,C1047";"SM0603";10;"47nF";;;
46;"C1045";"SM0402";1;"18pF";;;
47;"C809,C709,C647,C708,C646,C808";"SM0805";6;"100uF";;;
48;"U406,U1003,U405,U1004";"DFN8_3x3mm";4;"ADM7170ACPZ-3.3";;;
49;"C1023,C1010,C1011,C427,C1026,C1024,C1009,C415,C1025,C416,C1008,C428,C426,C414";"SM0805";14;"10uF";;;
50;"C410,C707,C802,C807,C701,C703,C411,C801,C804,C704,C101,C803,C806,C702,C706";"SM0402";15;"CAP_0402";;;
51;"J901,J101";"SMA_AMP_132255-12";2;"LO Ref output";;;
52;"C1042,C1046,C1043";"SM0402";3;"1nF";;;
53;"U1006,U1008,U409,U412,U410,U411,U408";"QFN-16_EP_3x3_Pitch0.5mm";7;"PE42553";;;
54;"U301";"TQFP-144_20x20mm_P0.5mm";1;"ICE40HX1K-TQ144";;;
55;"R1002,R1005,R1001,R404,R401";"SM0402";5;"4.7k";;;
56;"U414,U403,U402,U1012";"QFN24_4x4_0.5mm";4;"EP2C+";;;
57;"C548,C914,C919,C308,C307,C552,C320,C319,C902,C920,C928,C909,C901,C927,C550,C316,C926,C304,C311,C301,C317,C313,C555,C907,C305,C314,C302,C923,C929,C912,C911,C908,C549,C916,C906,C904,C310";"SM0402";37;"10nF";;;
58;"C1050,C205,C1056,C1053,C1051";"SM0805";5;"1uF";;;
59;"U1011";"QFN-16_EP_3x3_Pitch0.5mm";1;"PE42520";;;
60;"C208";"SM0603";1;"100nF";;;
61;"U1005";"QFN32_5x5mm_3.6mm";1;"ADF5355";;;
62;"C419,C1007";"SM0402";2;"33nF";;;
63;"L404,L406,L407,L1001,L1002,L405";"SM0402";6;"7.5nH";;;
64;"C454,C456,C457,C442,C1030,C1035,C435,C1054,C436,C1049,C1029,C458";"SM0402";12;"22pF";;;
65;"C1058,C1048,C451,C445,C449,C447,C1039,C453";"SM0402";8;"22p";;;
66;"R802,R701,R801,R610,R702,R609";"SM0402";6;"25";;;
67;"Q1001";"SOT-23";1;"BSS84";;;
68;"R405";"SM0603";1;"49";;;
69;"J1001";"CINCH_142-0701-881";1;"DUT_OUT_1";;;
70;"K402,K1001,K401";"DB1627";3;"TCM1-83X-1+";;;
71;"C1044";"SM0402";1;"5.6pF";;;
72;"F404,F1002";"FV1206";2;"LFCN-5000+";;;
73;"C705,C805";"SM0805";2;"CAP_0805";;;
74;"R901,R902,R402,R1003";"SM0402";4;"RES_0402";;;
75;"D301";"SOD-123";1;"DIODE";;;
76;"C202,C201,C207,C206";"SM1206";4;"10uF";;;
77;"L1004,L1005";"SM0805";2;"IND_0805";;;
78;"F401";"FV1206";1;"LFCN-2500+";;;
79;"C1006,C418";"SM0402";2;"390pF";;;
80;"U1002,U1001,U404";"DFN8_3x3mm";3;"ADM7170ACPZ-5.0";;;
81;"C1012,C420";"SM0402";2;"1500pF";;;
82;"R911,R912";"SM0402";2;"100";;;
83;"C204";"SM0805";1;"100nF";;;
84;"C551,C554";"SM0805";2;"4.7uF";;;
85;"U902";"SI5332A_QFN40_EP_5.9x5.9_Pitch0.5mm";1;"SI5332A-D-GM2";;;
86;"L408,L1006";"SM0603";2;"33n";;;
87;"L1003";"SM0402";1;"NC";;;
88;"U407";"QFN32_5x5mm_3.6mm";1;"ADF4355";;;
89;"U1007";"DQ849";1;"TSS-183A+";;;
90;"U901";"IQD_CFPT-126";1;"16.384MHz";;;
91;"R1006";"SM0603";1;"38";;;
92;"U1010";"SOT23-6";1;"LTC1983";;;
93;"U413,U1009";"SOT89-SKY65013-70";2;"SKY65013-70LF";;;
94;"F403";"FV1206";1;"LFCN-1400+";;;
95;"Q1002";"SOT-23";1;"BSS138";;;
96;"C918";"SM0402";1;"15pF";;;
97;"J1002";"CINCH_142-0701-881";1;"DUT_OUT_2";;;
98;"R202";"SM0402";1;"65k";;;
